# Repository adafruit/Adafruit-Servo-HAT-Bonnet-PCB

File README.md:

# Adafruit-Servo-HAT-Bonnet-PCB
PCB files for Adafruit Servo HAT and Bonnet

Format is EagleCAD schematic and board layout

For more details, check out the product pages at

   * http://www.adafruit.com/product/2327
   * https://www.adafruit.com/product/3416

Adafruit invests time and resources providing this open source design, 
please support Adafruit and open-source hardware by purchasing 
products from Adafruit!

Designed by Adafruit Industries.  
Creative Commons Attribution, Share-Alike license, check license.txt for more information
All text above must be included in any redistribution

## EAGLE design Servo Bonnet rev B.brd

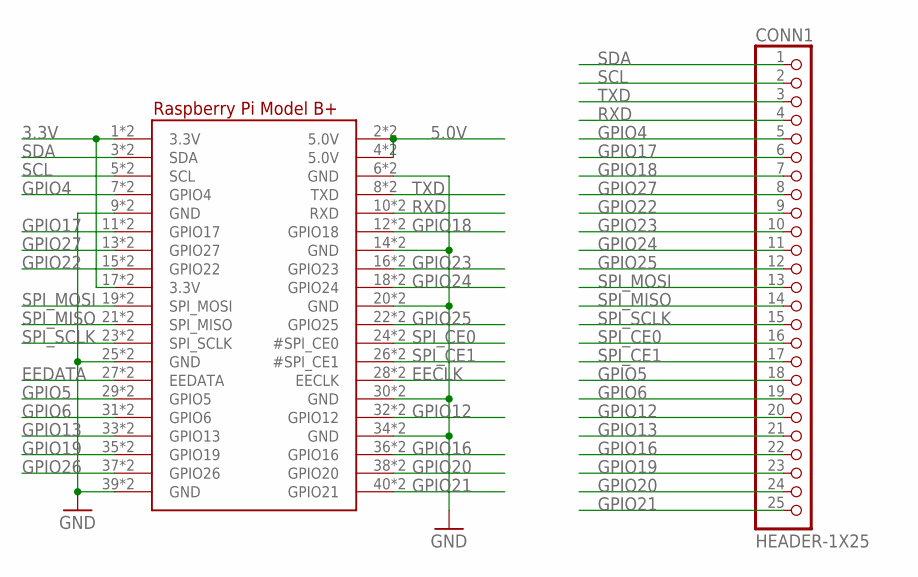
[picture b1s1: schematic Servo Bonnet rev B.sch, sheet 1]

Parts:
CONN1: HEADER-1X25; 1X25_ROUND_70MIL
RPI1: RASPBERRYPI_BPLUS_BONNET_THMSMT; PI_BONNET_THMSMT

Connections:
3.3V: RPI1.1 (3.3V), RPI1.17 (3.3V), RPI1.S1 (3.3V), RPI1.S17 (3.3V); also elsewhere on the board
5.0V: RPI1.2 (5.0V), RPI1.4 (5.0V), RPI1.S2 (5.0V), RPI1.S4 (5.0V); also elsewhere on the board
EECLK: RPI1.28 (EECLK), RPI1.S28 (EECLK)
EEDATA: RPI1.27 (EEDATA), RPI1.S27 (EEDATA)
GND: RPI1.6 (GND), RPI1.9 (GND), RPI1.14 (GND), RPI1.20 (GND), RPI1.25 (GND), RPI1.30 (GND), RPI1.34 (GND), RPI1.39 (GND), RPI1.S6 (GND), RPI1.S9 (GND), RPI1.S14 (GND), RPI1.S20 (GND), RPI1.S25 (GND), RPI1.S30 (GND), RPI1.S34 (GND), RPI1.S39 (GND); also elsewhere on the board
GPIO4: CONN1.5, RPI1.7 (GPIO4), RPI1.S7 (GPIO4)
GPIO5: CONN1.18, RPI1.29 (GPIO5), RPI1.S29 (GPIO5)
GPIO6: CONN1.19, RPI1.31 (GPIO6), RPI1.S31 (GPIO6)
GPIO12: CONN1.20, RPI1.32 (GPIO12), RPI1.S32 (GPIO12)
GPIO13: CONN1.21, RPI1.33 (GPIO13), RPI1.S33 (GPIO13)
GPIO16: CONN1.22, RPI1.36 (GPIO16), RPI1.S36 (GPIO16)
GPIO17: CONN1.6, RPI1.11 (GPIO17), RPI1.S11 (GPIO17)
GPIO18: CONN1.7, RPI1.12 (GPIO18), RPI1.S12 (GPIO18)
GPIO19: CONN1.23, RPI1.35 (GPIO19), RPI1.S35 (GPIO19)
GPIO20: CONN1.24, RPI1.38 (GPIO20), RPI1.S38 (GPIO20)
GPIO21: CONN1.25, RPI1.40 (GPIO21), RPI1.S40 (GPIO21)
GPIO22: CONN1.9, RPI1.15 (GPIO22), RPI1.S15 (GPIO22)
GPIO23: CONN1.10, RPI1.16 (GPIO23), RPI1.S16 (GPIO23)
GPIO24: CONN1.11, RPI1.18 (GPIO24), RPI1.S18 (GPIO24)
GPIO25: CONN1.12, RPI1.22 (GPIO25), RPI1.S22 (GPIO25)
GPIO26: RPI1.37 (GPIO26), RPI1.S37 (GPIO26)
GPIO27: CONN1.8, RPI1.13 (GPIO27), RPI1.S13 (GPIO27)
RXD: CONN1.4, RPI1.10 (RXD), RPI1.S10 (RXD)
SCL: CONN1.2, RPI1.5 (SCL), RPI1.S5 (SCL); also elsewhere on the board
SDA: CONN1.1, RPI1.3 (SDA), RPI1.S3 (SDA); also elsewhere on the board
SPI_CE0: CONN1.16, RPI1.24 (#SPI_CE0), RPI1.S24 (#SPI_CE0)
SPI_CE1: CONN1.17, RPI1.26 (#SPI_CE1), RPI1.S26 (#SPI_CE1)
SPI_MISO: CONN1.14, RPI1.21 (SPI_MISO), RPI1.S21 (SPI_MISO)
SPI_MOSI: CONN1.13, RPI1.19 (SPI_MOSI), RPI1.S19 (SPI_MOSI)
SPI_SCLK: CONN1.15, RPI1.23 (SPI_SCLK), RPI1.S23 (SPI_SCLK)
TXD: CONN1.3, RPI1.8 (TXD), RPI1.S8 (TXD)

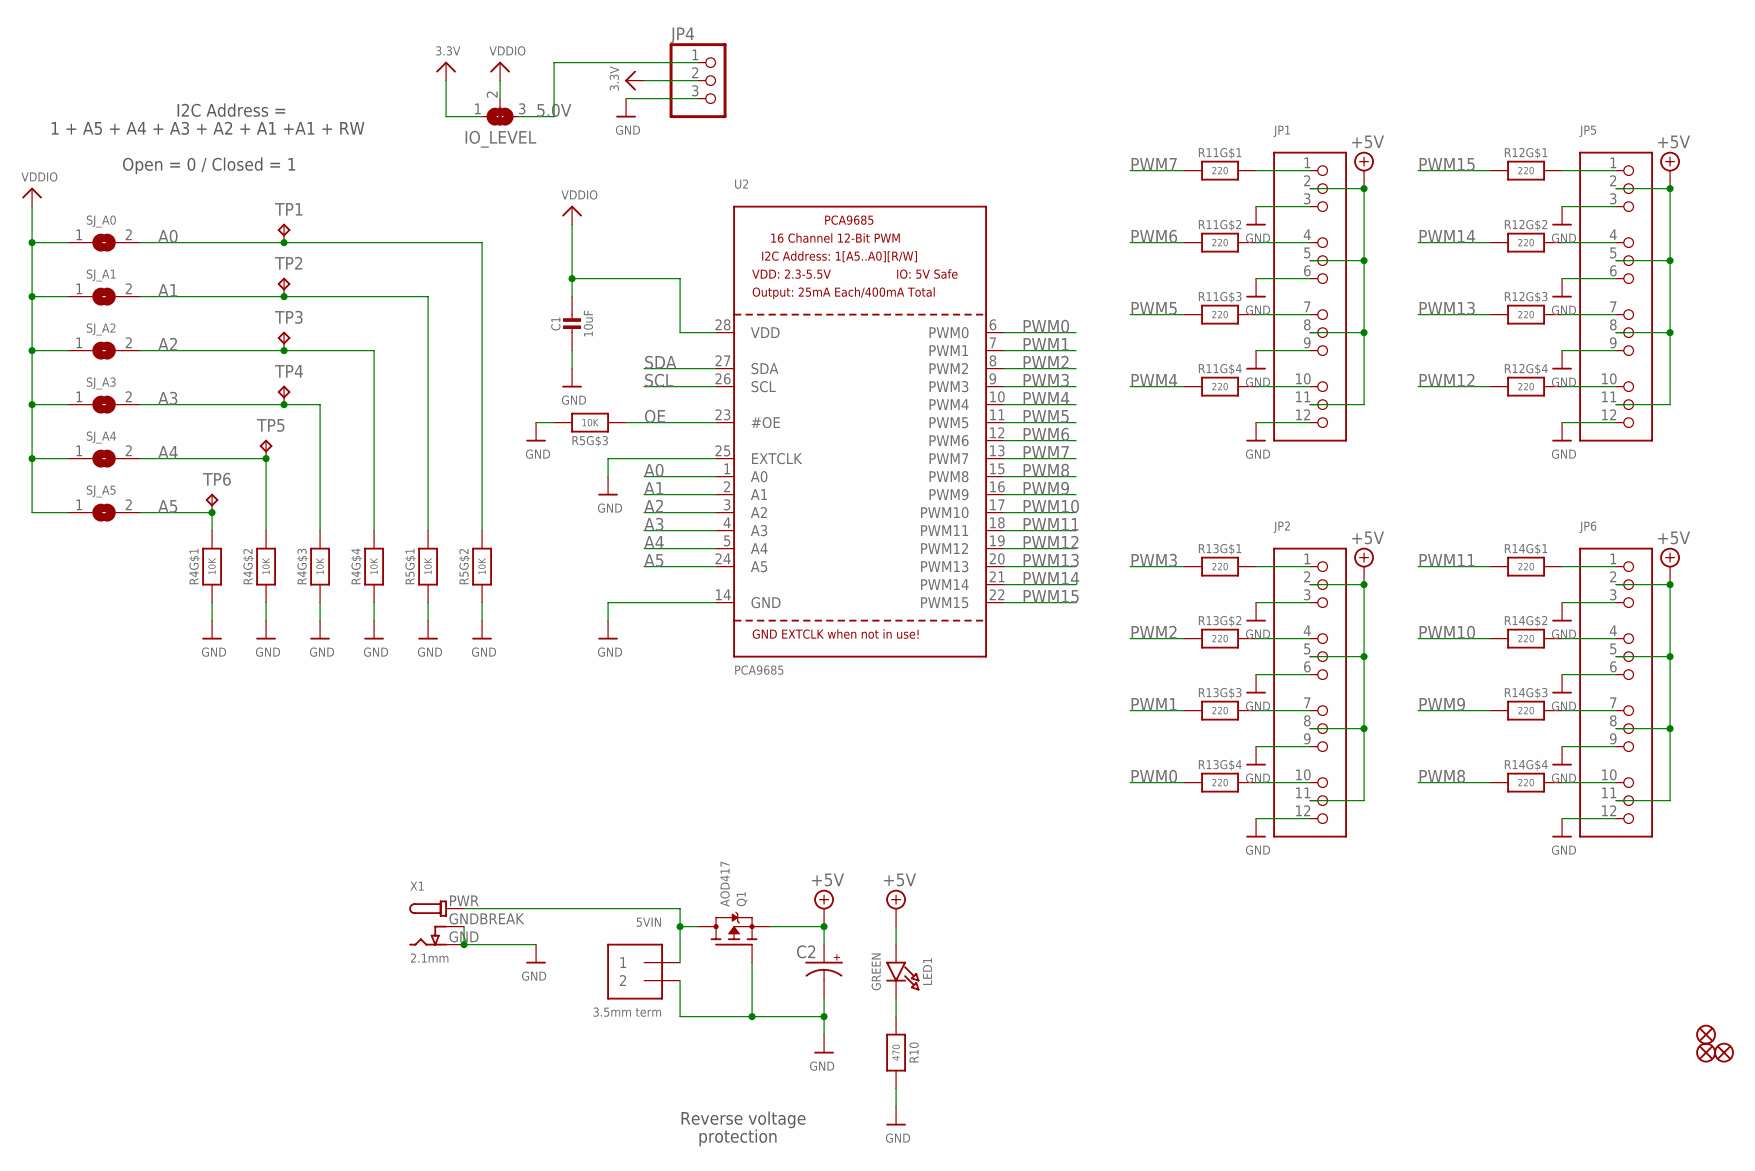
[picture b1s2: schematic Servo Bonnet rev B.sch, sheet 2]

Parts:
5VIN: 3.5mm term; TERMBLOCK_1X2-3.5MM
C1: 10uF; 0805-NO
C2: CPOL-USE3.5-8; E3,5-8
FID1, FID2, FID3: FIDUCIAL_1MM
IO_LEVEL: SOLDERJUMPER_2WAY; SOLDERJUMPER_2WAY_OPEN_NOPASTE
JP1, JP2, JP5, JP6: HEADER-3X04; 3X04
JP4: HEADER-1X3ROUND; 1X03_ROUND
LED1: GREEN; CHIPLED_0805_NOOUTLINE
Q1: AOD417; TO252
R4, R5: 10K; RESPACK_4X0603
R10: 470; 0603-NO
R11, R12, R13, R14: 220; RESPACK_4X0603
SJ_A0, SJ_A1, SJ_A2, SJ_A3, SJ_A4, SJ_A5: SOLDERJUMPERREFLOW_NOPASTE; SOLDERJUMPER_REFLOW_NOPASTE
TP1, TP2, TP3, TP4, TP5, TP6: TPB1,27; B1,27
U2: PCA9685; TSSOP28
X1: 2.1mm; DCJACK_2MM_PTH

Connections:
3.3V: IO_LEVEL.1, JP4.2; also elsewhere on the board
5.0V: IO_LEVEL.3, JP4.1; also elsewhere on the board
+5V: C2.+, JP1.2, JP1.5, JP1.8, JP1.11, JP2.2, JP2.5, JP2.8, JP2.11, JP5.2, JP5.5, JP5.8, JP5.11, JP6.2, JP6.5, JP6.8, JP6.11, LED1.A, Q1.2 (S)
A0: R5.7 (2), SJ_A0.2, TP1.TP, U2.1 (A0)
A1: R5.8 (2), SJ_A1.2, TP2.TP, U2.2 (A1)
A2: R4.5 (2), SJ_A2.2, TP3.TP, U2.3 (A2)
A3: R4.6 (2), SJ_A3.2, TP4.TP, U2.4 (A3)
A4: R4.7 (2), SJ_A4.2, TP5.TP, U2.5 (A4)
A5: R4.8 (2), SJ_A5.2, TP6.TP, U2.24 (A5)
GND: 5VIN.2, C1.2, C2.-, JP1.3, JP1.6, JP1.9, JP1.12, JP2.3, JP2.6, JP2.9, JP2.12, JP4.3, JP5.3, JP5.6, JP5.9, JP5.12, JP6.3, JP6.6, JP6.9, JP6.12, Q1.1 (G), R4.1, R4.2 (1), R4.3 (1), R4.4 (1), R5.1, R5.2 (1), R5.6 (2), R10.2, U2.14 (GND), U2.25 (EXTCLK), X1.GND, X1.GNDBREAK; also elsewhere on the board
unnamed: LED1.C, R10.1
unnamed: JP1.4, R11.7 (2)
unnamed: JP1.1, R11.8 (2)
unnamed: JP1.7, R11.6 (2)
unnamed: JP1.10, R11.5 (2)
unnamed: JP2.1, R13.8 (2)
unnamed: JP2.4, R13.7 (2)
unnamed: JP2.7, R13.6 (2)
unnamed: JP2.10, R13.5 (2)
unnamed: JP6.10, R14.5 (2)
unnamed: JP6.7, R14.6 (2)
unnamed: JP6.4, R14.7 (2)
unnamed: JP6.1, R14.8 (2)
unnamed: JP5.10, R12.5 (2)
unnamed: JP5.7, R12.6 (2)
unnamed: JP5.4, R12.7 (2)
unnamed: JP5.1, R12.8 (2)
OE: R5.3 (1), U2.23 (#OE)
PWM0: R13.4 (1), U2.6 (PWM0)
PWM1: R13.3 (1), U2.7 (PWM1)
PWM2: R13.2 (1), U2.8 (PWM2)
PWM3: R13.1, U2.9 (PWM3)
PWM4: R11.4 (1), U2.10 (PWM4)
PWM5: R11.3 (1), U2.11 (PWM5)
PWM6: R11.2 (1), U2.12 (PWM6)
PWM7: R11.1, U2.13 (PWM7)
PWM8: R14.4 (1), U2.15 (PWM8)
PWM9: R14.3 (1), U2.16 (PWM9)
PWM10: R14.2 (1), U2.17 (PWM10)
PWM11: R14.1, U2.18 (PWM11)
PWM12: R12.4 (1), U2.19 (PWM12)
PWM13: R12.3 (1), U2.20 (PWM13)
PWM14: R12.2 (1), U2.21 (PWM14)
PWM15: R12.1, U2.22 (PWM15)
PWR: 5VIN.1, Q1.3 (D), X1.PWR
SCL: U2.26 (SCL); also elsewhere on the board
SDA: U2.27 (SDA); also elsewhere on the board
VDDIO: C1.1, IO_LEVEL.2, SJ_A0.1, SJ_A1.1, SJ_A2.1, SJ_A3.1, SJ_A4.1, SJ_A5.1, U2.28 (VDD)

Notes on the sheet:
Reverse voltage
protection
1 + A5 + A4 + A3 + A2 + A1 +A1 + RW
I2C Address =
Open = 0 / Closed = 1

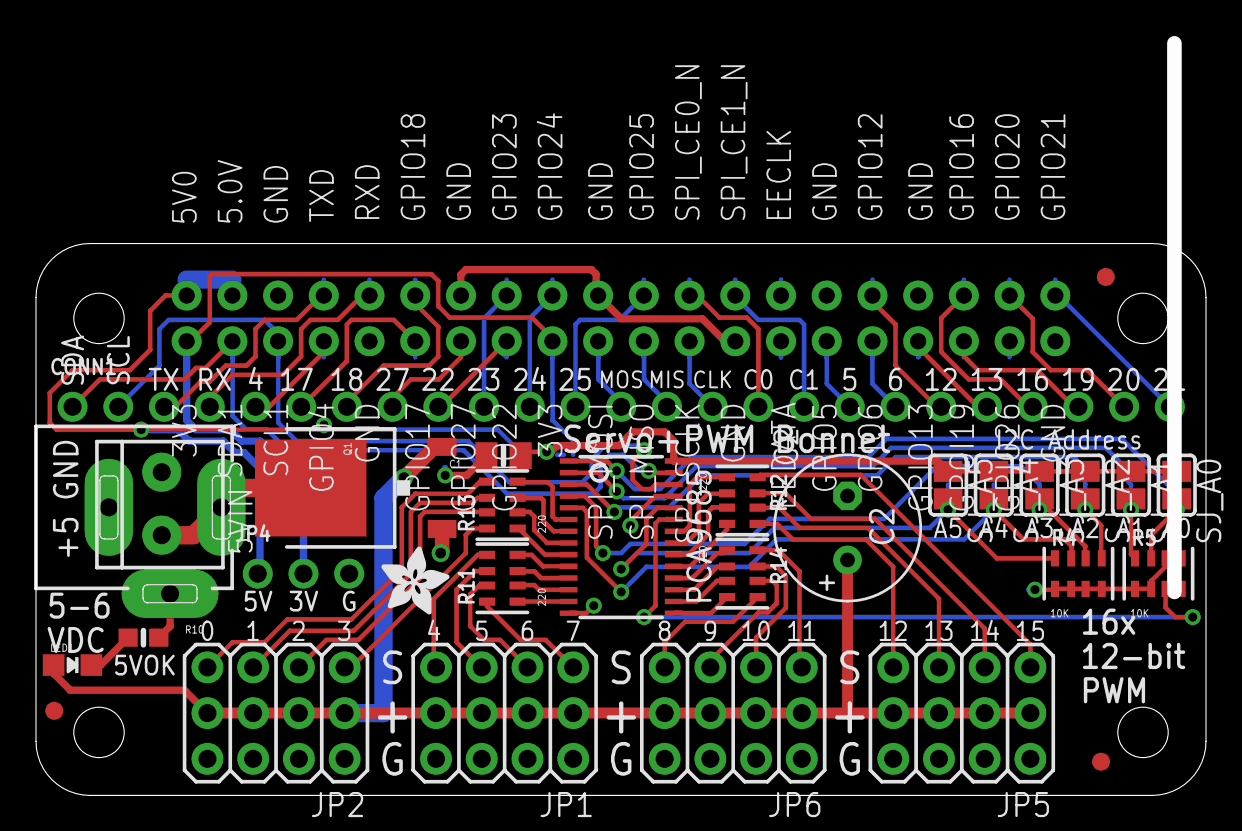
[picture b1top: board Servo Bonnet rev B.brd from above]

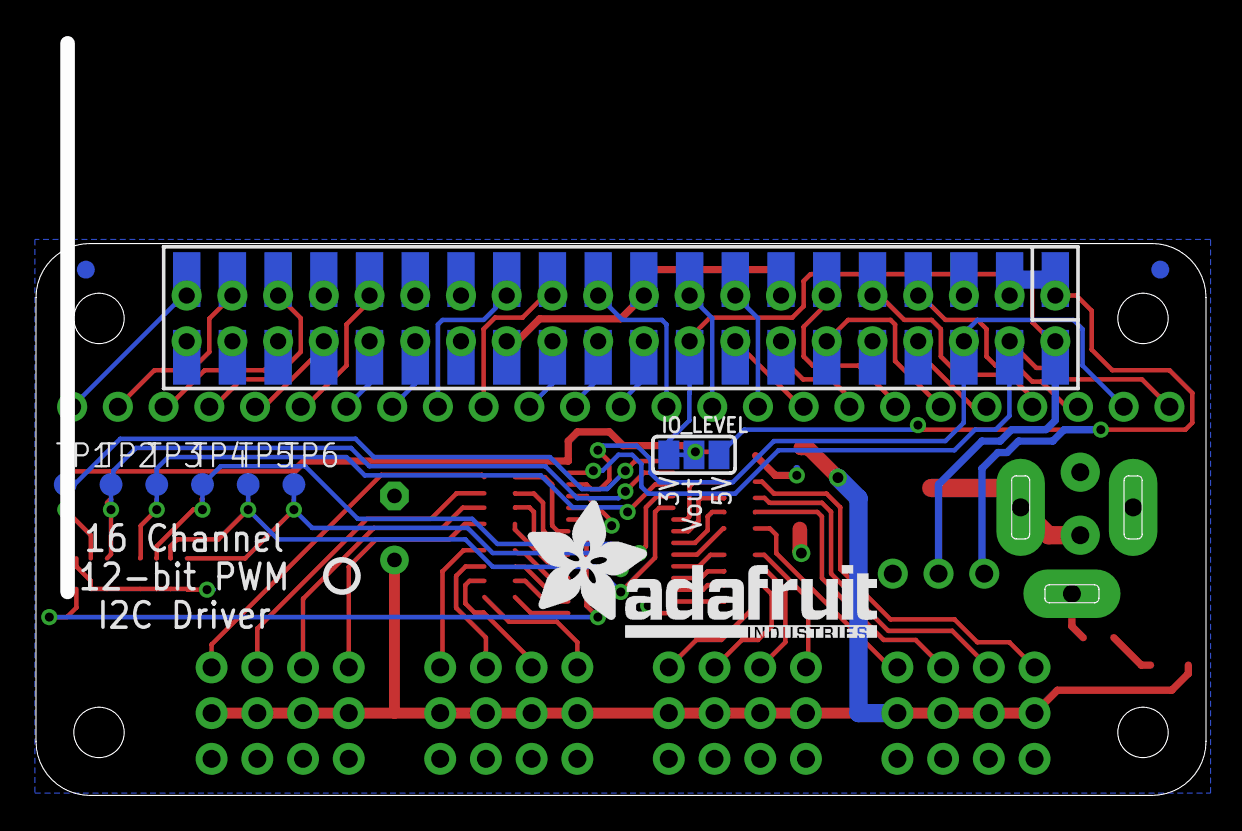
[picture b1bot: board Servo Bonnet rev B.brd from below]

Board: 2 copper layers, 64.2 x 41.4 mm, 40 parts (9 on the bottom side), 74 nets.

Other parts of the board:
U$6: ADAFRUIT_TEXT_20MM
U$8: ADAFRUIT_3.5MM
U$11: PCBFEAT-REV-040

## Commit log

2015-09-21 init
2015-09-21 read me
2019-01-09 added bonnet to readme
2019-01-09 adding bonnet files

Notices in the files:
parts and their libraries:
microbuilder: This work is placed in the public domain, and may be freely used for commercial and non-commercial work with the following conditions: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
